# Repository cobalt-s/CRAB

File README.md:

# CRAB
A quad pod robot we are building using ESP-32 for the brain with MG90S Servos controlled by the PCA9685 Servo Driver.

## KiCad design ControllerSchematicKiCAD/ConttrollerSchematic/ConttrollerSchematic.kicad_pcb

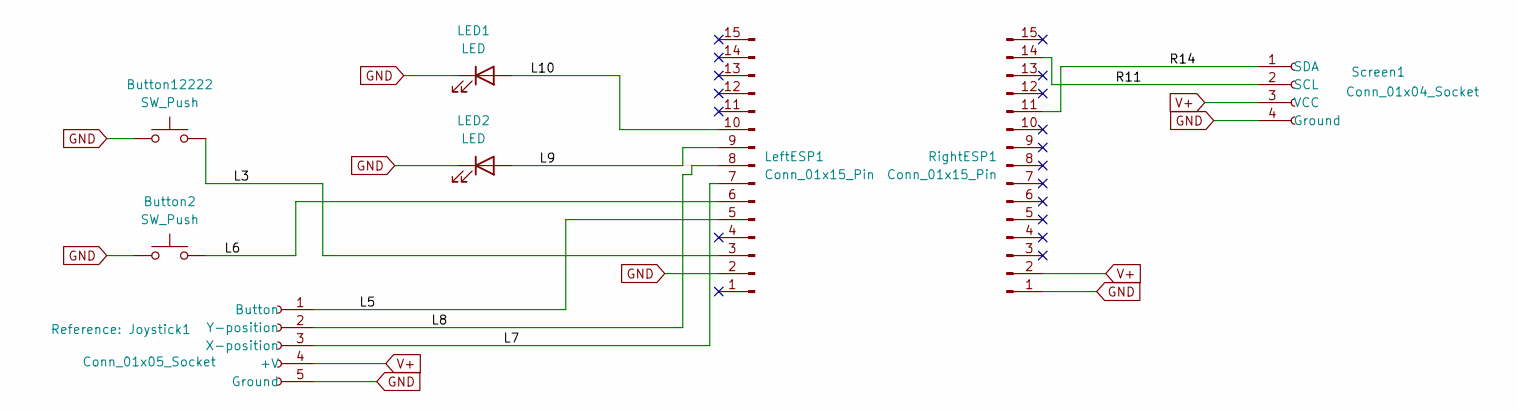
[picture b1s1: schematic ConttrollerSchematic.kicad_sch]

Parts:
Button2, Button12222: SW_Push; SW_Push_1P1T-SH_NO_CK_KMR2xxG
Joystick1: Conn_01x05_Socket; PinSocket_1x05_P2.54mm_Horizontal
LED1, LED2: LED; LED_D5.0mm
LeftESP1: Conn_01x15_Pin; PinSocket_1x15_P2.54mm_Vertical
RightESP1: Conn_01x15_Pin; PinSocket_1x15_P2.54mm_Vertical
Screen1: Conn_01x04_Socket; PinSocket_1x04_P1.00mm_Vertical

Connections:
/L3: Button12222.2, LeftESP1.3
/L5: Joystick1.1 (Button), LeftESP1.5
/L6: Button2.2, LeftESP1.6
/L7: Joystick1.3 (X-position), LeftESP1.7
/L8: Joystick1.2 (Y-position), LeftESP1.8
/L9: LED2.2 (A), LeftESP1.9
/L10: LED1.2 (A), LeftESP1.10
/R11: RightESP1.14, Screen1.2 (SCL)
/R14: RightESP1.11, Screen1.1 (SDA)
GND: Button2.1, Button12222.1, Joystick1.5 (Ground), LED1.1 (K), LED2.1 (K), LeftESP1.2, RightESP1.1, Screen1.4 (Ground)
V+: Joystick1.4 (+V), RightESP1.2, Screen1.3 (VCC)

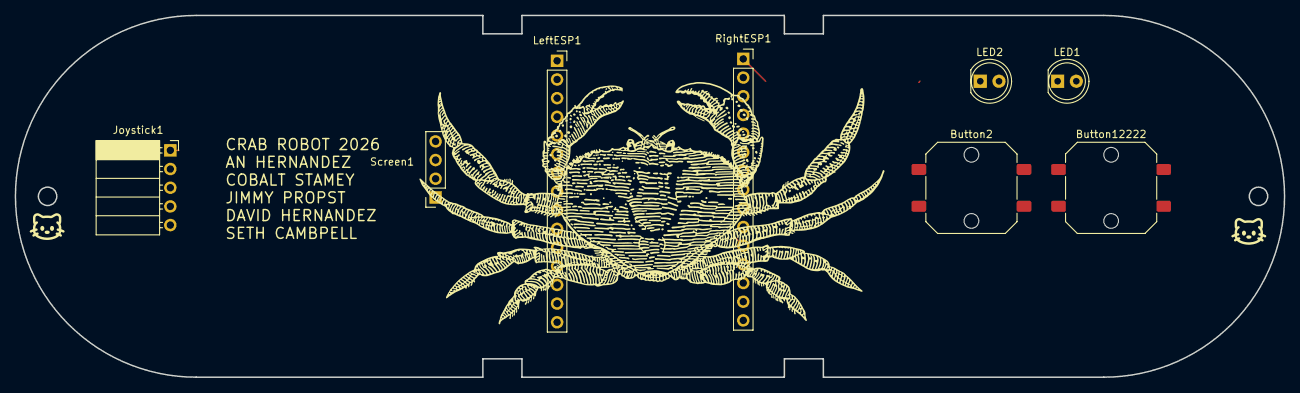
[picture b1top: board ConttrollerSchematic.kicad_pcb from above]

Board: 2 copper layers, 172.6 x 49.2 mm, 8 parts (0 on the bottom side), 11 nets.

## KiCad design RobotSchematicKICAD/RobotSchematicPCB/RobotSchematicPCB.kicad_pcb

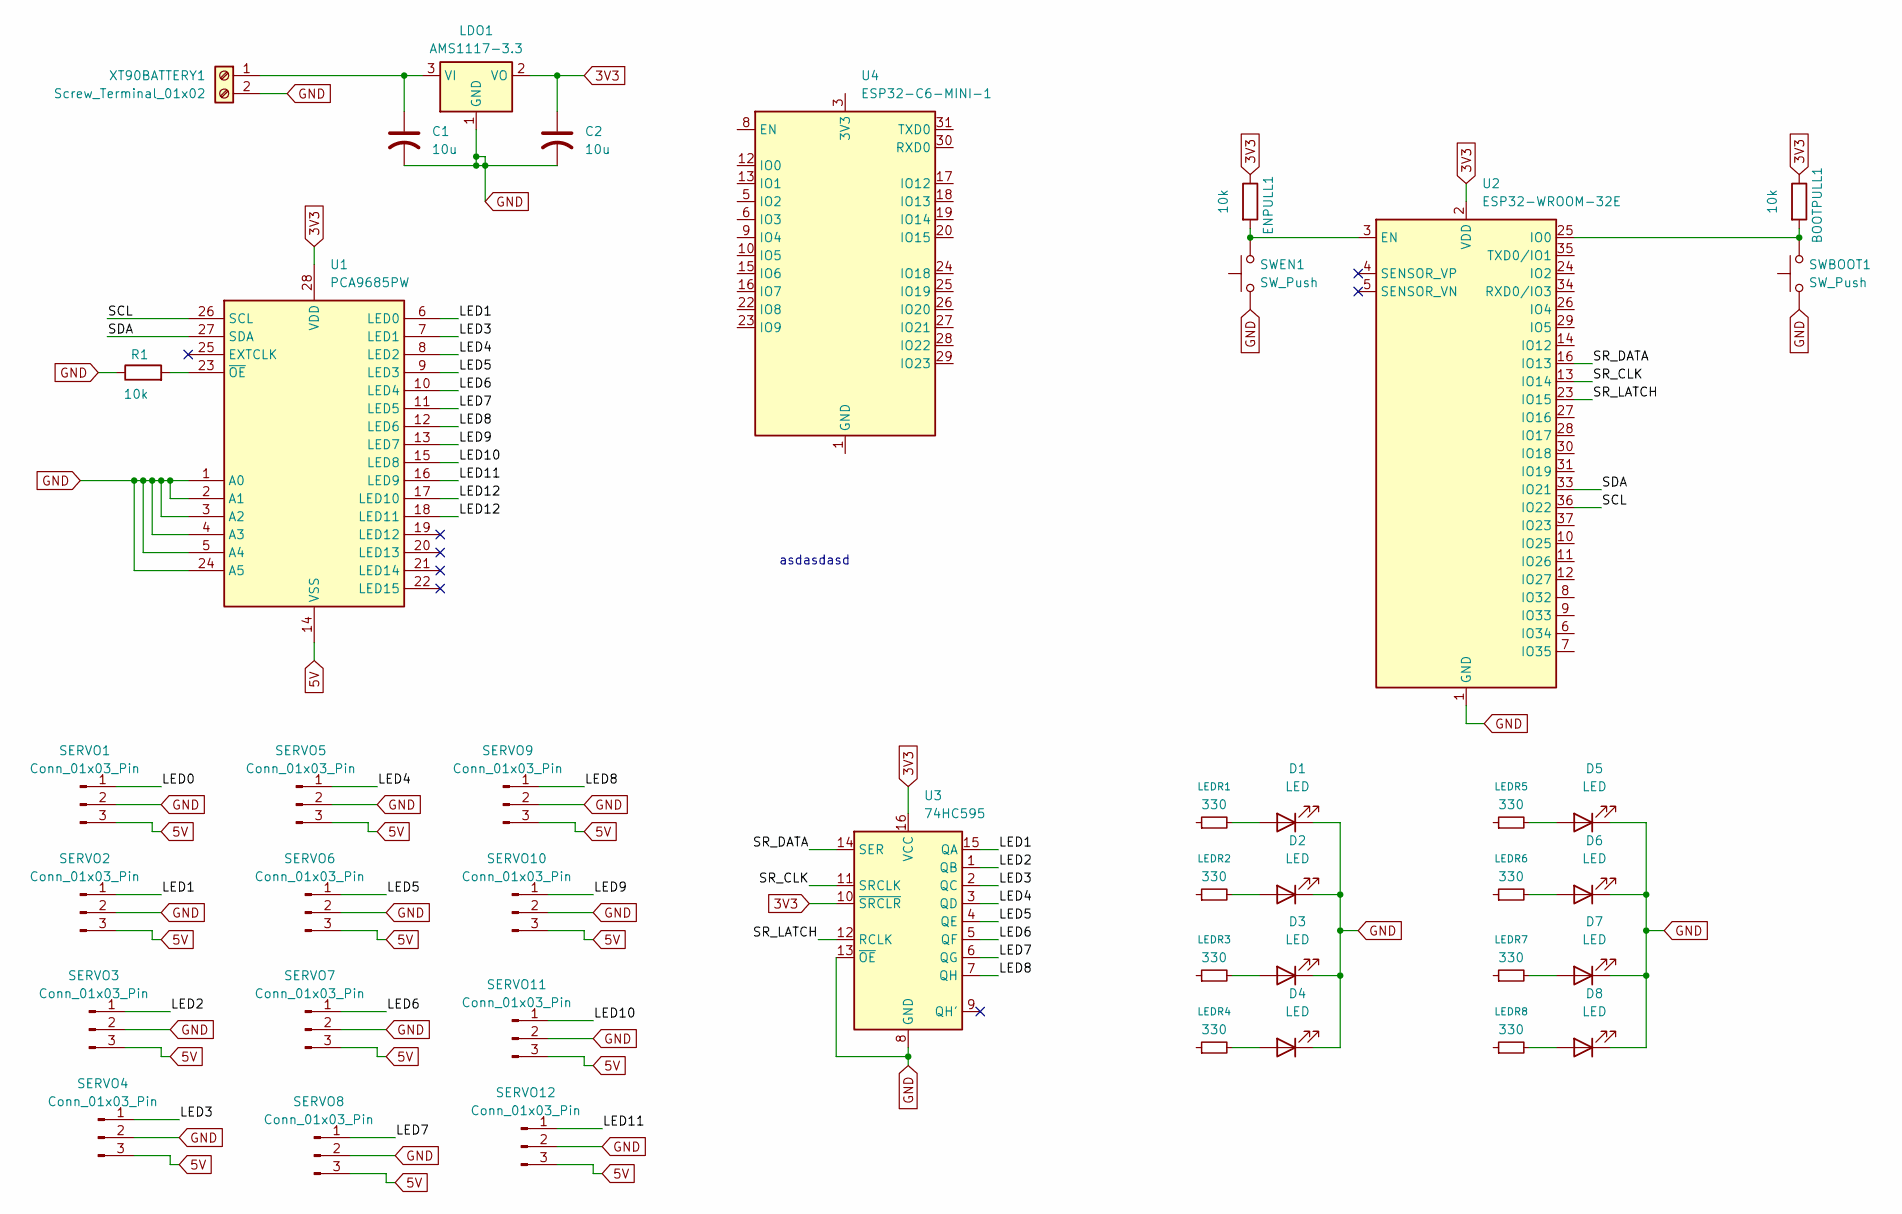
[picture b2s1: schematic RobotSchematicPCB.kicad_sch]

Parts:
BOOTPULL1: 10k; R_0603_1608Metric
C1, C2: 10u; C_0603_1608Metric
D1, D2, D3, D4, D5, D6, D7, D8: LED; LED_D3.0mm
ENPULL1: 10k; R_0603_1608Metric
LDO1: AMS1117-3.3; R_0201_0603Metric
LEDR1, LEDR2, LEDR3, LEDR4, LEDR5, LEDR6, LEDR7, LEDR8: 330; R_0603_1608Metric
R1: 10k; R_0603_1608Metric
SERVO1, SERVO2, SERVO3, SERVO4, SERVO5, SERVO6, SERVO7, SERVO8, SERVO9, SERVO10, SERVO11, SERVO12: Conn_01x03_Pin; Harwin_M20-89003xx_1x03_P2.54mm_Horizontal
SWBOOT1: SW_Push; SW_PUSH_6mm
SWEN1: SW_Push; SW_PUSH_6mm
U1: PCA9685PW; TSSOP-28_4.4x9.7mm_P0.65mm
U2: ESP32-WROOM-32E; ESP32-WROOM-32D
U3: 74HC595; SOIC-16_3.9x9.9mm_P1.27mm
U4: ESP32-C6-MINI-1
XT90BATTERY1: Screw_Terminal_01x02; PhoenixContact_GMSTB_2,5_2-GF-7,62_1x02_P7.62mm_Horizontal_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

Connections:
3V3: BOOTPULL1.1, C2.1, ENPULL1.1, LDO1.2 (VO), U1.28 (VDD), U2.2 (VDD), U3.10 (~SRCLR), U3.16 (VCC)
5V: SERVO1.3, SERVO2.3, SERVO3.3, SERVO4.3, SERVO5.3, SERVO6.3, SERVO7.3, SERVO8.3, SERVO9.3, SERVO10.3, SERVO11.3, SERVO12.3, U1.14 (VSS)
/LED0: SERVO1.1
/LED1: SERVO2.1, U1.6 (LED0), U3.15 (QA)
/LED2: SERVO3.1, U3.1 (QB)
/LED3: SERVO4.1, U1.7 (LED1), U3.2 (QC)
/LED4: SERVO5.1, U1.8 (LED2), U3.3 (QD)
/LED5: SERVO6.1, U1.9 (LED3), U3.4 (QE)
/LED6: SERVO7.1, U1.10 (LED4), U3.5 (QF)
/LED7: SERVO8.1, U1.11 (LED5), U3.6 (QG)
/LED8: SERVO9.1, U1.12 (LED6), U3.7 (QH)
/LED9: SERVO10.1, U1.13 (LED7)
/LED10: SERVO11.1, U1.15 (LED8)
/LED11: SERVO12.1, U1.16 (LED9)
/LED12: U1.17 (LED10), U1.18 (LED11)
/SCL: U1.26 (SCL), U2.36 (IO22)
/SDA: U1.27 (SDA), U2.33 (IO21)
/SR_CLK: U2.13 (IO14), U3.11 (SRCLK)
/SR_DATA: U2.16 (IO13), U3.14 (SER)
/SR_LATCH: U2.23 (IO15), U3.12 (RCLK)
GND: C1.2, C2.2, D1.1 (K), D2.1 (K), D3.1 (K), D4.1 (K), D5.1 (K), D6.1 (K), D7.1 (K), D8.1 (K), LDO1.1 (GND), R1.1, SERVO1.2, SERVO2.2, SERVO3.2, SERVO4.2, SERVO5.2, SERVO6.2, SERVO7.2, SERVO8.2, SERVO9.2, SERVO10.2, SERVO11.2, SERVO12.2, SWBOOT1.1, SWEN1.1, U1.1 (A0), U1.2 (A1), U1.3 (A2), U1.4 (A3), U1.5 (A4), U1.24 (A5), U2.1 (GND), U2.15 (GND), U2.38 (GND), U2.39 (GND), U3.8 (GND), U3.13 (~OE), XT90BATTERY1.2
unnamed: D1.2 (A), LEDR1.2
unnamed: D2.2 (A), LEDR2.2
unnamed: D3.2 (A), LEDR3.2
unnamed: D4.2 (A), LEDR4.2
unnamed: D5.2 (A), LEDR5.2
unnamed: D6.2 (A), LEDR6.2
unnamed: D7.2 (A), LEDR7.2
unnamed: D8.2 (A), LEDR8.2
unnamed: C1.1, LDO1.3 (VI), XT90BATTERY1.1
unnamed: R1.2, U1.23 (~OE)
unnamed: ENPULL1.2, SWEN1.2, U2.3 (EN)
unnamed: BOOTPULL1.2, SWBOOT1.2, U2.25 (IO0)
unnamed: U4.1 (GND), U4.2 (GND), U4.11 (GND), U4.14 (GND), U4.36 (GND), U4.37 (GND), U4.38 (GND), U4.39 (GND), U4.40 (GND), U4.41 (GND), U4.42 (GND), U4.43 (GND), U4.44 (GND), U4.45 (GND), U4.46 (GND), U4.47 (GND), U4.48 (GND), U4.49 (GND), U4.50 (GND), U4.51 (GND), U4.52 (GND), U4.53 (GND)

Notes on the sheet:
asdasdasd

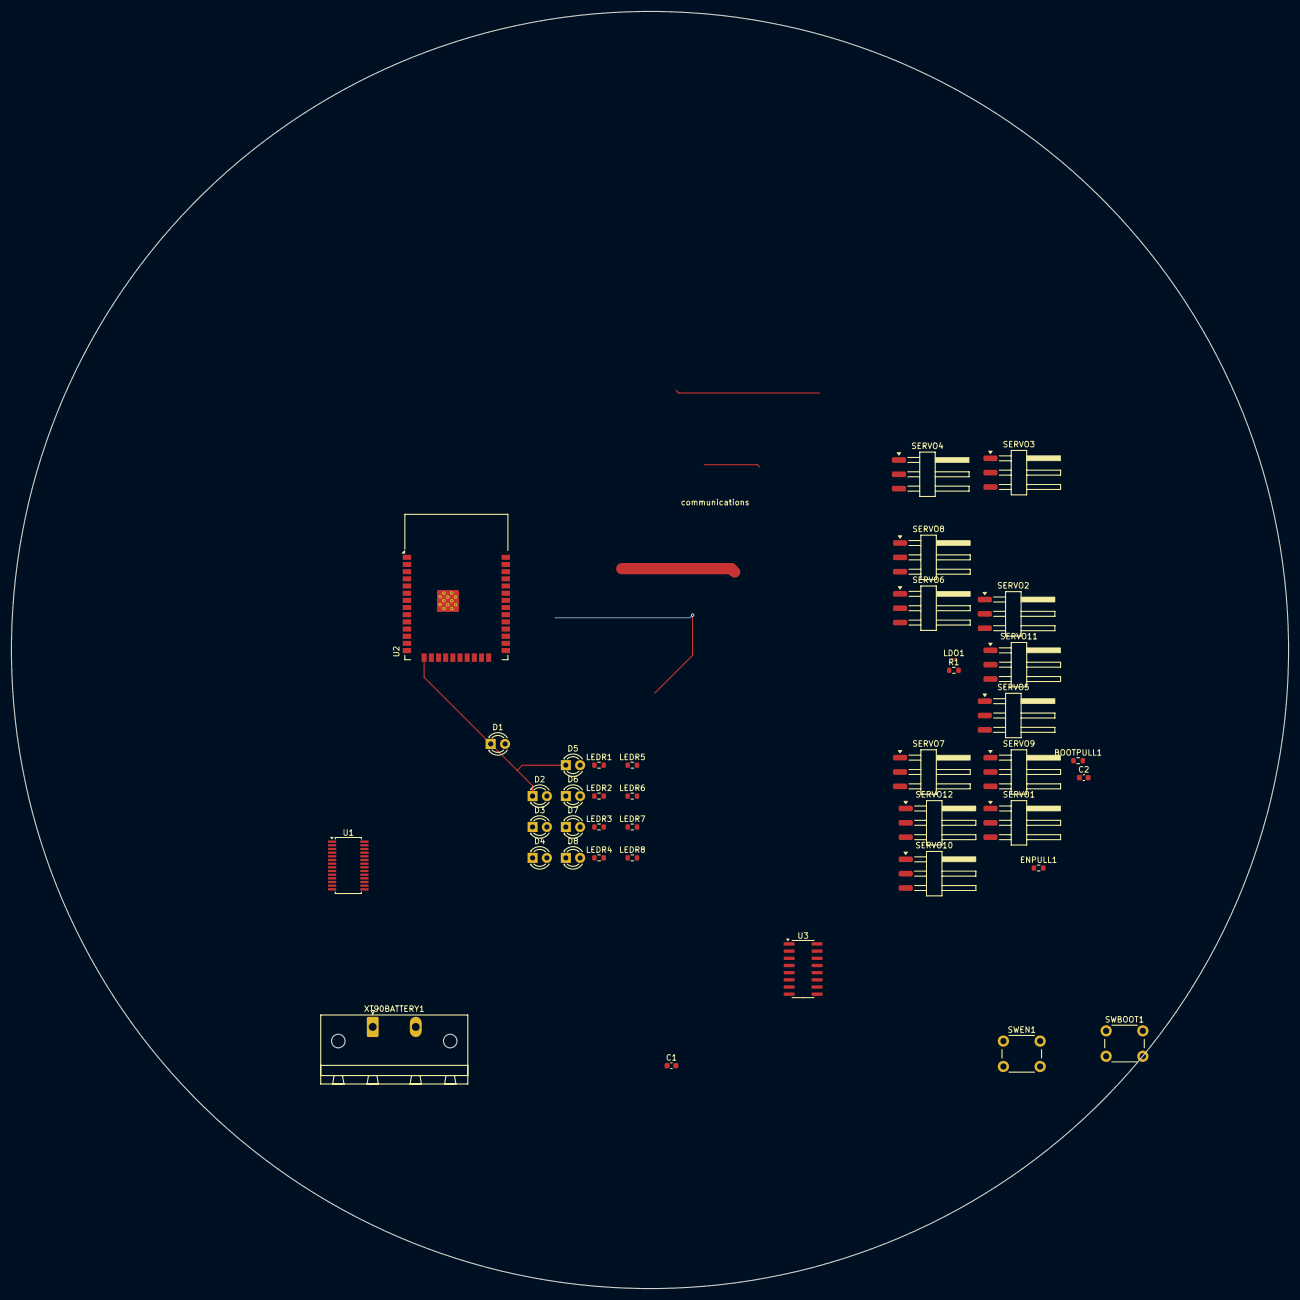
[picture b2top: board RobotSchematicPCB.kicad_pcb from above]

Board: 2 copper layers, 226.1 x 226.1 mm, 40 parts (0 on the bottom side), 32 nets.

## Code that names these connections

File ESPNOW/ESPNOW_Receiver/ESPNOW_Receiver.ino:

#include <WiFi.h>
#include <esp_now.h>

// LED pins
#define LED1 25
#define LED2 26
#define LED3 32
#define LED4 33

typedef struct message {
  uint8_t buttonID;
} message;

message receivedData;

// Correct callback signature for ESP32 IDF v5.x
void onReceive(const esp_now_recv_info *info,
               const uint8_t *incomingData,
               int len) {

  memcpy(&receivedData, incomingData, sizeof(receivedData));

  // Turn off all LEDs
  digitalWrite(LED1, LOW);
  digitalWrite(LED2, LOW);
  digitalWrite(LED3, LOW);
  digitalWrite(LED4, LOW);

  // Turn on the LED corresponding to buttonID
  switch (receivedData.buttonID) {
    case 1: digitalWrite(LED1, HIGH); break;
    case 2: digitalWrite(LED2, HIGH); break;
    case 3: digitalWrite(LED3, HIGH); break;
    case 4: digitalWrite(LED4, HIGH); break;
  }

  Serial.print("Received button: ");
  Serial.println(receivedData.buttonID);
}

void setup() {
  Serial.begin(9600);
  delay(1000); // Wait for Serial Monitor

  // Setup LEDs
  pinMode(LED1, OUTPUT);
  pinMode(LED2, OUTPUT);
  pinMode(LED3, OUTPUT);
  pinMode(LED4, OUTPUT);

  // Wi-Fi station mode
  WiFi.mode(WIFI_STA);
  delay(500); // allow MAC to initialize

  // Print MAC address (for transmitter)
  Serial.print("Receiver MAC: ");
  Serial.println(WiFi.macAddress());

  // Initialize ESP-NOW
  esp_err_t result = esp_now_init();
  if (result != ESP_OK) {
    Serial.print("ESP-NOW init failed, error code: ");
    Serial.println(result);
    return;
  }

  // Register receive callback with correct signature
  esp_now_register_recv_cb(onReceive);

  Serial.println("Receiver Ready");
}

void loop() {
  // Nothing needed; ESP-NOW callback handles LED updates
}

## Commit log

2025-10-11 fixed up the formatting, added some TODO's to the remote control code
2025-10-11 fixed the () in the if statement
2025-10-11 fixed up the formatting, added some TODO's to the remote control code (#1)
    * fixed up the formatting, added some TODO's to the remote control code
    * fixed the () in the if statement
2025-10-17 I add a feature when you pushed a button it said something on the screen
2025-10-17 I add a feature when you pushed a button it said something on the screen (#2)
2025-11-08 added code for buttons and fixed some bugs
2025-11-14 Enhance project description in README.md
2026-01-18 ESPNOW Functioning Code
    I made the ESPNOW work. Next step: make remote controller work with ESPNOW example.
2026-01-22 Update RemoteControlCode.ino
    I updated the code! (well actually an ) ready for renzo
2026-01-22 Update RemoteControlCode.ino
    whoa I did things
2026-02-12 Changed controller code to be more method based
2026-02-18 integrated renzos espNow transmitter code to the controller.
2026-04-07 Refactor remote control Arduino sketch
    Clean up and refactor RemoteControlCode.ino for readability and maintainability. Key changes: rename pins and constants to clear names, introduce ControllerMessage struct and outgoingData, consolidat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
2026-04-08 Rename transmitter sketch; add debug & LED
    Rename RemoteControlCode.ino to RemoteControlTransmitter/RemoteControlTransmitter.ino and introduce debug/fault-handling changes. Added TODO notes for buzzer and screen, new LED pin constants (LED_1,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
2026-04-08 Add ESP-NOW remote receiver sketch
    added a receiver code right now its just renzos code from his branch.
    and then I put the transmitter code in its own folder. the past commit it was renamed wrong lol so there was some confusion.
2026-04-08 added some temp receiver code
    I took renzos code for the receiver and abstracted a little bit. I then used claude to create some abstracted functions that we can implement ourselves. Thats where all the TODOs are.
2026-04-08 Added screen implementation to the code
2026-04-08 made debugDisplay more clean
2026-04-08 robot schematic
    this is the kicad folder
2026-04-08 added a capacitor for testing
2026-04-08 folder for kicad
    asdasd
2026-04-08 added the project
    pcb
2026-04-18 Ignore macOS .DS_Store files
    Add .DS_Store to .gitignore to prevent committing macOS Finder metadata. The .DS_Store file in the working tree was modified in this changeset; to remove the currently tracked file from the repo, run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
2026-04-23 Schematic updates
    lots of stuff
2026-04-23 Schematic updates (#4)
    lots of stuff
2026-04-29 auto routed
    heheh
2026-04-29 moved something
    moved the esp
2026-05-10 added some to robot pcb
    I added the pca, esp, leds, servos, and some buttons, and did some wiring.
2026-05-13 I changed the location of some stuff redo the button size
    Changed buttons footprint, delete all wiring for now
2026-05-13 changed the dimension
2026-05-13 something more
2026-05-31 imported from 3d model for exact dimensions
    I imported the dxf from the model for the controller and then I made that the edge cuts for the board. I also added some art
